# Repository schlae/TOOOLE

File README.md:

# FLOOB TOOOLE - Fluke 700013 Analog Switch Replacement
Several old Fluke multimeters (and potentially other equipment as well) use this custom chip made by Fluke called the 700013. It's just a quad SPST analog switch chip but the control lines are latched and also pass through an AND gate. There's no off-the-shelf equivalent chip, and these chips are known to be unreliable.

So I cloned the chip using a simple circuit that fits on a tiny circuit board. The new design uses any off-the-shelf DG412 or equivalent (industry standard pinout). To implement a 4-bit transparent latch, the design uses a 74157 quad 2-input mux with one set of inputs connected to the data coming in and the other set of inputs connected to the *outputs* of the mux to recirculate the data and latch it.

I've tested the board in my Fluke 8840A as a replacement for two of the chips in the ohms section, and it seems to work fine. I have not tested it in any of the other sections.

By the way, since the DG412 footprint is industry standard, feel free to substite it with your favorite quad analog switch. If yours uses active low control inputs, you can swap U2 with a 74AHCT00.

Check out the [schematic](https://github.com/schlae/TOOOLE/blob/main/TOOOLE.pdf)

## Bill of Materials

| Des | Mouser part number | Description |
|-----|--------------------|-------------|
| U1  | 78-DG412DQ-T1-E3   | Quad analog switch, SPST |
| U2  | 771-AHCT08PW118    | Quad AND gate |
| U3  | 771-AHCT157PW118   | Quad 2-1 line multiplexer |
| C1  | (generic)          | 0.1uF 25V X5R 0603 ceramic capacitor |
| R1  | (generic)          | 1K ohm 5% 0603 carbon resistor |
| Q1  | 512-2N7002L        | n-channel MOSFET, SOT23 (can be subbed) |
| J1  | (generic)          | 20x DIP pins (flip pins or others) |

## Assembly Instructions

Build the board using your favorite board vendor. I'm in the United States so I just sent the KiCAD board file directly to [OSH Park](https://oshpark.com/). The grand total was $3.40 for 3 boards, including shipping.

Solder the surface mount components first, then install the Flip Pins (but you could also use wires soldered into a machine-pin DIP socket). Be sure to clean the board thoroughly with isopropyl alcohol, since any residue will increase the leakage current of the DG412.

You can test it on a breadboard first, which might be a good idea if you aren't sure about the quality of the solder joints. I'd recommend installing a socket in your Fluke instrument, and then plugging the board into the socket.

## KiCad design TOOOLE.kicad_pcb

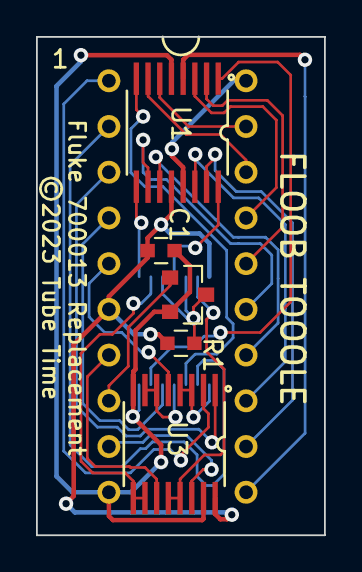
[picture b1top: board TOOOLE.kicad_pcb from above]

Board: 2 copper layers, 16.0 x 27.7 mm, 7 parts (1 on the bottom side), 29 nets.

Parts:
C1: 0.1uF; CAPC1608X100
J1: Conn_02x10_Counter_Clockwise; DIP20
Q1: 2N7002; SOT95P230X117-3
R1: 1K; RESC1608X55
U1: DG412xUE; TSOP65P640X110-16
U2: SN74AHCT157PWR; TSOP65P640X110-14
U3: 74LS157; TSOP65P640X110-16

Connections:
+5V: C1.1, J1.6, R1.1, U1.12 (VL), U2.14 (VCC), U3.16 (VCC)
/DB_A: J1.1, U3.2 (I0a)
/DB_B: J1.5, U3.5 (I0b)
/DB_C: J1.7, U3.11 (I0c)
/DB_D: J1.9, U3.14 (I0d)
/EN_A: J1.2, U2.2
/EN_B: J1.4, U2.5
/~EN_CD: J1.8, Q1.1 (G)
/~LATCH: J1.3, U3.1 (S)
GND: C1.2, J1.10, Q1.2 (S), U1.5 (GND), U2.7 (GND), U3.8 (GND), U3.15 (E)
unnamed: J1.12, U1.15
unnamed: J1.13, U1.14
unnamed: J1.14, U1.11
unnamed: J1.15, U1.10
unnamed: J1.16, U1.2
unnamed: J1.17, U1.3
unnamed: J1.18, U1.7
unnamed: J1.19, U1.6
unnamed: Q1.3 (D), R1.2, U2.10, U2.12
unnamed: U1.1, U2.6
unnamed: U1.8, U2.3
unnamed: U1.9, U2.8
unnamed: U1.16, U2.11
unnamed: U2.1, U3.3 (I1a), U3.4 (Za)
unnamed: U2.4, U3.6 (I1b), U3.7 (Zb)
unnamed: U2.9, U3.9 (Zc), U3.10 (I1c)
unnamed: U2.13, U3.12 (Zd), U3.13 (I1d)
VDD: J1.20, U1.13 (V+)
VEE: J1.11, U1.4 (V-)

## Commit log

2023-07-01 Initial version

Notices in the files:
TOOOLE.kicad_pcb:
http://creativecommons.org/licenses/by-sa/4.0
This work is licensed under the Creative Commons Attribution-ShareAlike
Copyright (C) 2023 Tube Time
©2023 Tube Time
